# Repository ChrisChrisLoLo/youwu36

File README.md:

# youwu36

## About
36 key gasket mounted ortholinear keyboard that can be used with the miryoku layout. More details will come as design stabilizes. 

## Status
The current PCBs work! I'm am now confident enough to start rolling out build instructions, case files, and qmk software

## Handwired
There is a handwired case available that I'm fairly happy with. You can find it in the `./case` directory

## Attribution
All emojis designed by OpenMoji – the open-source emoji and icon project. License: CC BY-SA 4.0

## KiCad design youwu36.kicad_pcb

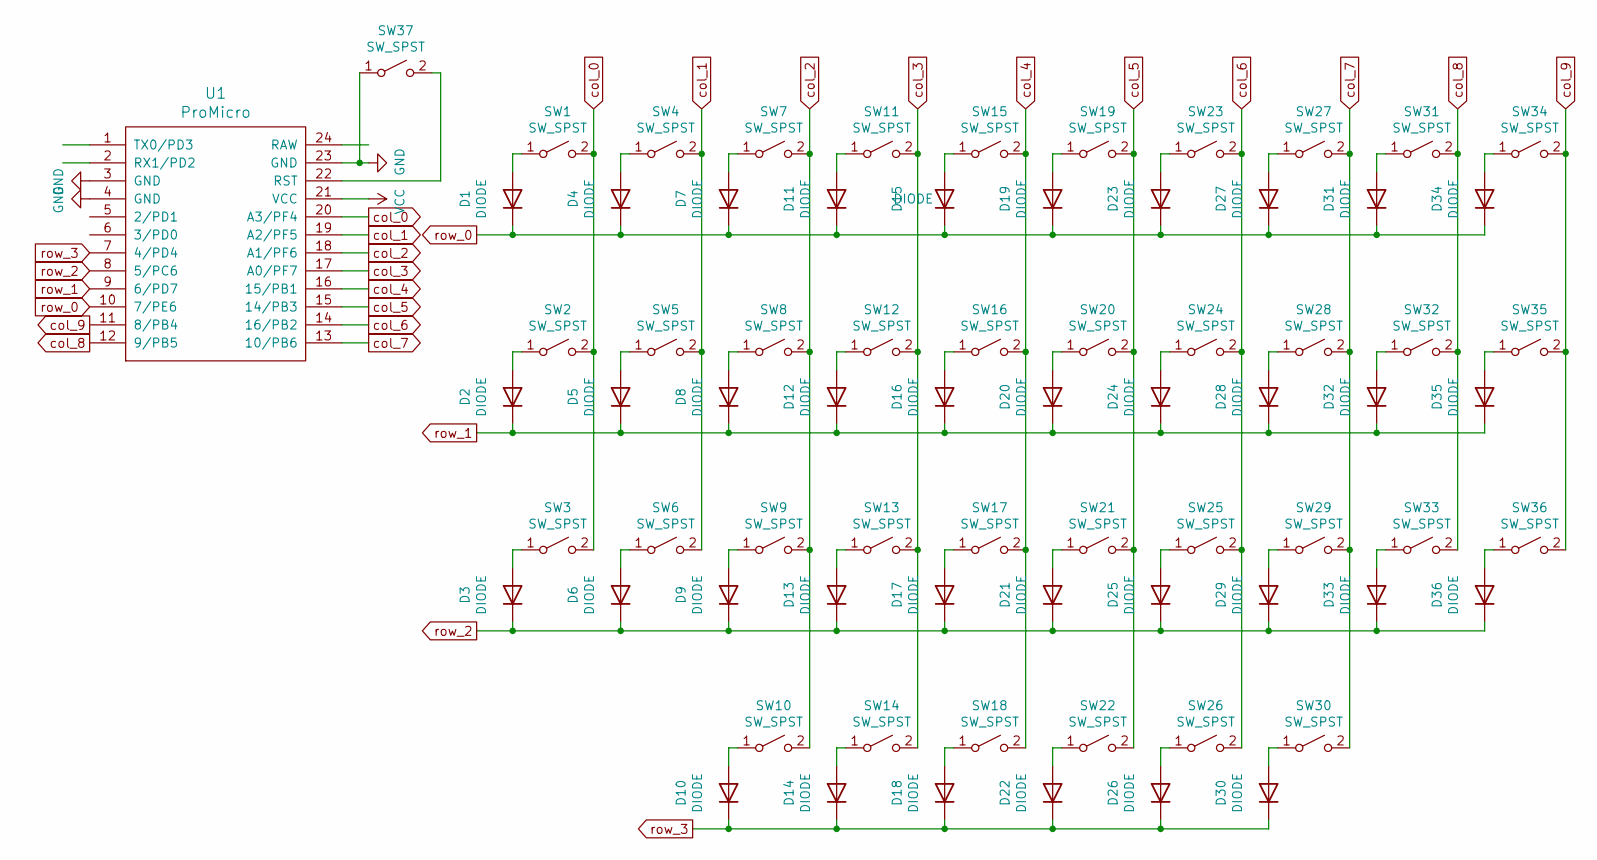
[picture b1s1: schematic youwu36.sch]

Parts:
D1, D2, D3, D4, D5, D6, D7, D8, D9, D10, D11, D12, D13, D14, D15, D16, D17, D18, D19, D20, D21, D22, D23, D24, D25, D26, D27, D28, D29, D30, D31, D32, D33, D34, D35, D36: DIODE; D_SOD-123
SW1, SW2, SW3, SW4, SW5, SW6, SW7, SW8, SW9, SW10, SW11, SW12, SW13, SW14, SW15, SW16, SW17, SW18, SW19, SW20, SW21, SW22, SW23, SW24, SW25, SW26, SW27, SW28, SW29, SW30, SW31, SW32, SW33, SW34, SW35, SW36: SW_SPST; Kailh_socket_MX
SW37: SW_SPST; SW_SPST_EVQPE1
U1: ProMicro; ArduinoProMicro

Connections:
GND: SW37.1 (A), U1.3 (GND), U1.4 (GND), U1.23 (GND)
unnamed: D1.2 (A), SW1.1 (A)
unnamed: D2.2 (A), SW2.1 (A)
unnamed: D3.2 (A), SW3.1 (A)
unnamed: D4.2 (A), SW4.1 (A)
unnamed: D5.2 (A), SW5.1 (A)
unnamed: D6.2 (A), SW6.1 (A)
unnamed: D7.2 (A), SW7.1 (A)
unnamed: D8.2 (A), SW8.1 (A)
unnamed: D9.2 (A), SW9.1 (A)
unnamed: D10.2 (A), SW10.1 (A)
unnamed: D11.2 (A), SW11.1 (A)
unnamed: D12.2 (A), SW12.1 (A)
unnamed: D13.2 (A), SW13.1 (A)
unnamed: D14.2 (A), SW14.1 (A)
unnamed: D15.2 (A), SW15.1 (A)
unnamed: D16.2 (A), SW16.1 (A)
unnamed: D17.2 (A), SW17.1 (A)
unnamed: D18.2 (A), SW18.1 (A)
unnamed: D19.2 (A), SW19.1 (A)
unnamed: D20.2 (A), SW20.1 (A)
unnamed: D21.2 (A), SW21.1 (A)
unnamed: D22.2 (A), SW22.1 (A)
unnamed: D23.2 (A), SW23.1 (A)
unnamed: D24.2 (A), SW24.1 (A)
unnamed: D25.2 (A), SW25.1 (A)
unnamed: D26.2 (A), SW26.1 (A)
unnamed: D27.2 (A), SW27.1 (A)
unnamed: D28.2 (A), SW28.1 (A)
unnamed: D29.2 (A), SW29.1 (A)
unnamed: D30.2 (A), SW30.1 (A)
unnamed: D31.2 (A), SW31.1 (A)
unnamed: D32.2 (A), SW32.1 (A)
unnamed: D33.2 (A), SW33.1 (A)
unnamed: D34.2 (A), SW34.1 (A)
unnamed: D35.2 (A), SW35.1 (A)
unnamed: D36.2 (A), SW36.1 (A)
unnamed: SW37.2 (B), U1.22 (RST)
VCC: U1.21 (VCC)
col_0: SW1.2 (B), SW2.2 (B), SW3.2 (B), U1.20 (A3/PF4)
col_1: SW4.2 (B), SW5.2 (B), SW6.2 (B), U1.19 (A2/PF5)
col_2: SW7.2 (B), SW8.2 (B), SW9.2 (B), SW10.2 (B), U1.18 (A1/PF6)
col_3: SW11.2 (B), SW12.2 (B), SW13.2 (B), SW14.2 (B), U1.17 (A0/PF7)
col_4: SW15.2 (B), SW16.2 (B), SW17.2 (B), SW18.2 (B), U1.16 (15/PB1)
col_5: SW19.2 (B), SW20.2 (B), SW21.2 (B), SW22.2 (B), U1.15 (14/PB3)
col_6: SW23.2 (B), SW24.2 (B), SW25.2 (B), SW26.2 (B), U1.14 (16/PB2)
col_7: SW27.2 (B), SW28.2 (B), SW29.2 (B), SW30.2 (B), U1.13 (10/PB6)
col_8: SW31.2 (B), SW32.2 (B), SW33.2 (B), U1.12 (9/PB5)
col_9: SW34.2 (B), SW35.2 (B), SW36.2 (B), U1.11 (8/PB4)
row_0: D1.1 (K), D4.1 (K), D7.1 (K), D11.1 (K), D15.1 (K), D19.1 (K), D23.1 (K), D27.1 (K), D31.1 (K), D34.1 (K), U1.10 (7/PE6)
row_1: D2.1 (K), D5.1 (K), D8.1 (K), D12.1 (K), D16.1 (K), D20.1 (K), D24.1 (K), D28.1 (K), D32.1 (K), D35.1 (K), U1.9 (6/PD7)
row_2: D3.1 (K), D6.1 (K), D9.1 (K), D13.1 (K), D17.1 (K), D21.1 (K), D25.1 (K), D29.1 (K), D33.1 (K), D36.1 (K), U1.8 (5/PC6)
row_3: D10.1 (K), D14.1 (K), D18.1 (K), D22.1 (K), D26.1 (K), D30.1 (K), U1.7 (4/PD4)

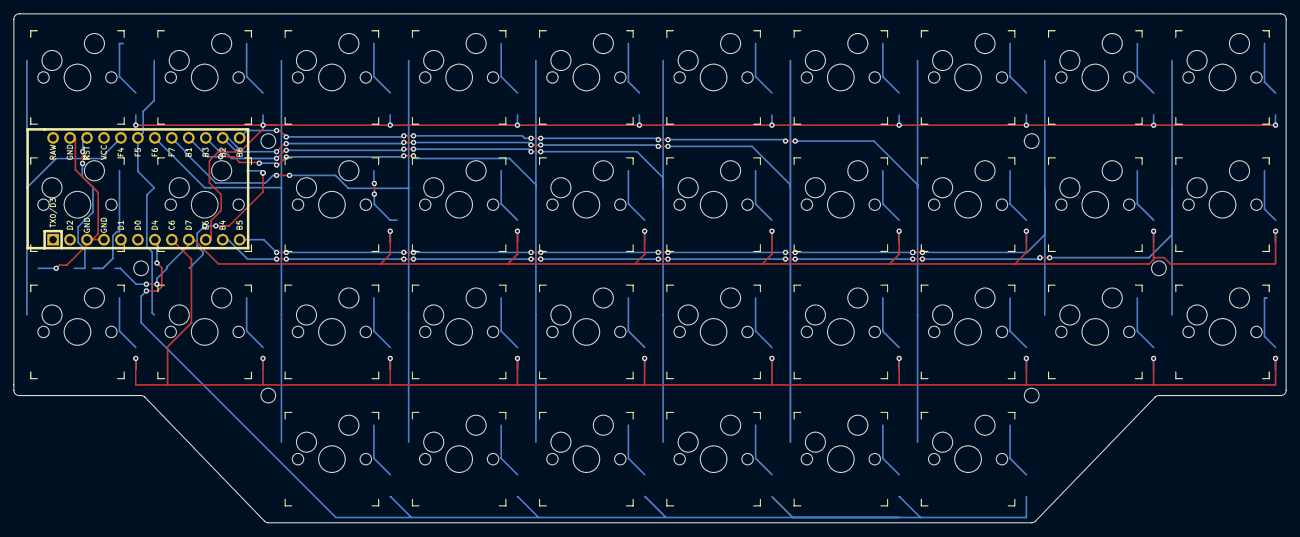
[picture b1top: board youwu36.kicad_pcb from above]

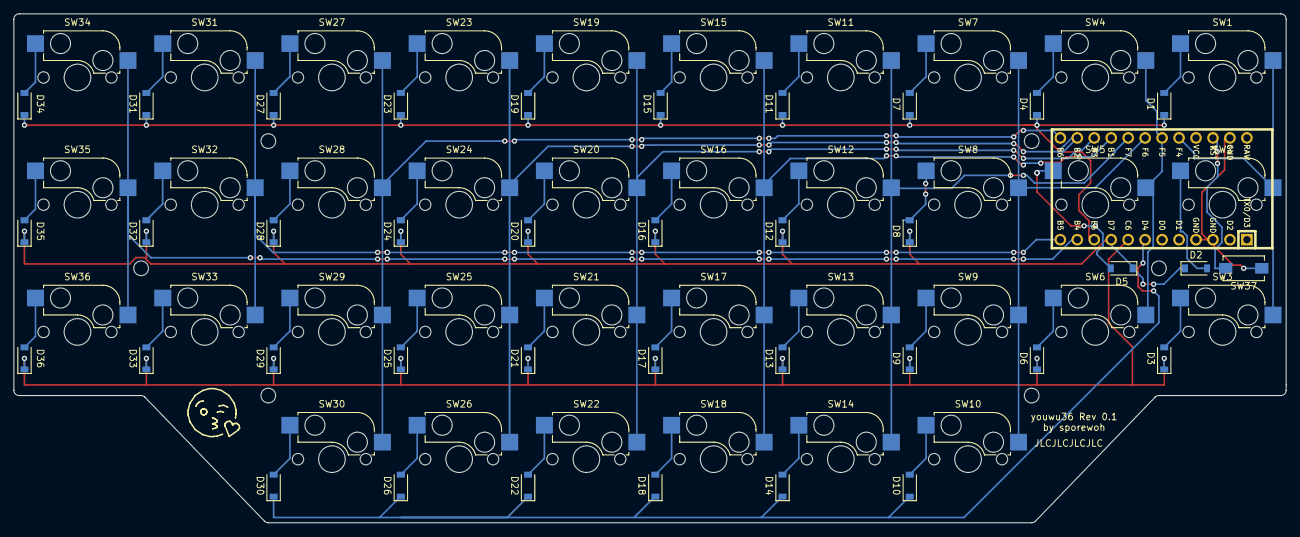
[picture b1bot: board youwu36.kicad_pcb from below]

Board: 2 copper layers, 190.5 x 76.2 mm, 74 parts (37 on the bottom side), 52 nets.

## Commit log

2022-02-08 add README
2022-02-13 add case files
2022-02-21 update readmes, remove old outlines
2022-03-02 add images folder
2022-03-02 Add image
    Sent from my iphone
2022-03-20 Add attribution to README
